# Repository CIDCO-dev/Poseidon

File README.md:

# Poseidon
Hydrographic surveying platform operating system (ROS Noetic).

## Getting started (RPi4, Ubuntu 20.04, ROS Noetic)
- Clone under `/opt`: `sudo chown $USER:$USER /opt && cd /opt && git clone --recursive <repo>`
- Install: run `install/rpi4-noetic.sh` (RPi4 target).
- Build: `cd /opt/Poseidon/src/workspace && catkin_make -j1 -DCATKIN_BLACKLIST_PACKAGES="mavros;inertial_sense;velodyne;ins_piksi;velodyne_pointcloud;velodyne_driver;velodyne_laserscan;gnss_mosaic_x5;tf"`
- Source: `source /opt/ros/noetic/setup.bash` then `source /opt/Poseidon/src/workspace/devel/setup.bash`.
- Launch simulator: `roslaunch launch/Simulator/dummy_simulator_virtual-machine.launch`, then open the web UI at `http://localhost`.

## Docs
Full documentation lives in `doc/` (Markdown):
- `doc/README.md`: overview, build, run, tests
- `doc/install.md`: installation with dependencies (RPi4, Ubuntu 20.04, ROS Noetic)

## Tests
- C++/Python/ROS: `catkin_make run_tests -j1 -DCATKIN_BLACKLIST_PACKAGES="ins_piksi;libmavconn;echoboat_odometry;mavros_msgs;mavros;mavros_extras;test_mavros;gnss_mosaic_x5;imu_bno055;sonar_imagenex852;inertial_sense;raspberrypi_vitals;imu_null;sonar_dummy;gnss_dummy;lidar_filtering"`
- JS: `cd www/webroot/js && npm test --coverage`

## Tools
- Rosbag replay: `roslaunch launch/Echoboat/rosbag_replay.launch bag_filename:=rosbag.bag`
- Lidar georef: `./devel/lib/logger/lidarGeoreferencer -h` (supports filtering options)
- Logging modes: 1=Always ON, 2=Manual, 3=Speed based

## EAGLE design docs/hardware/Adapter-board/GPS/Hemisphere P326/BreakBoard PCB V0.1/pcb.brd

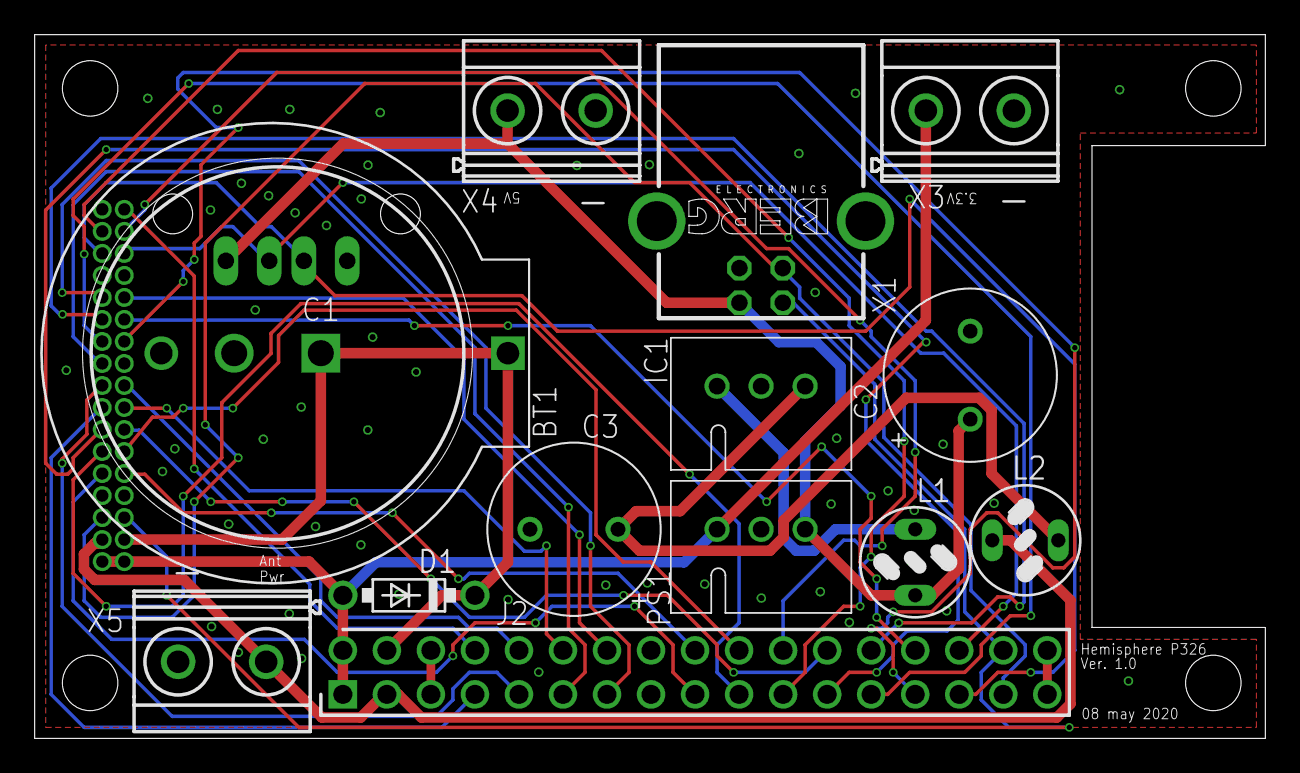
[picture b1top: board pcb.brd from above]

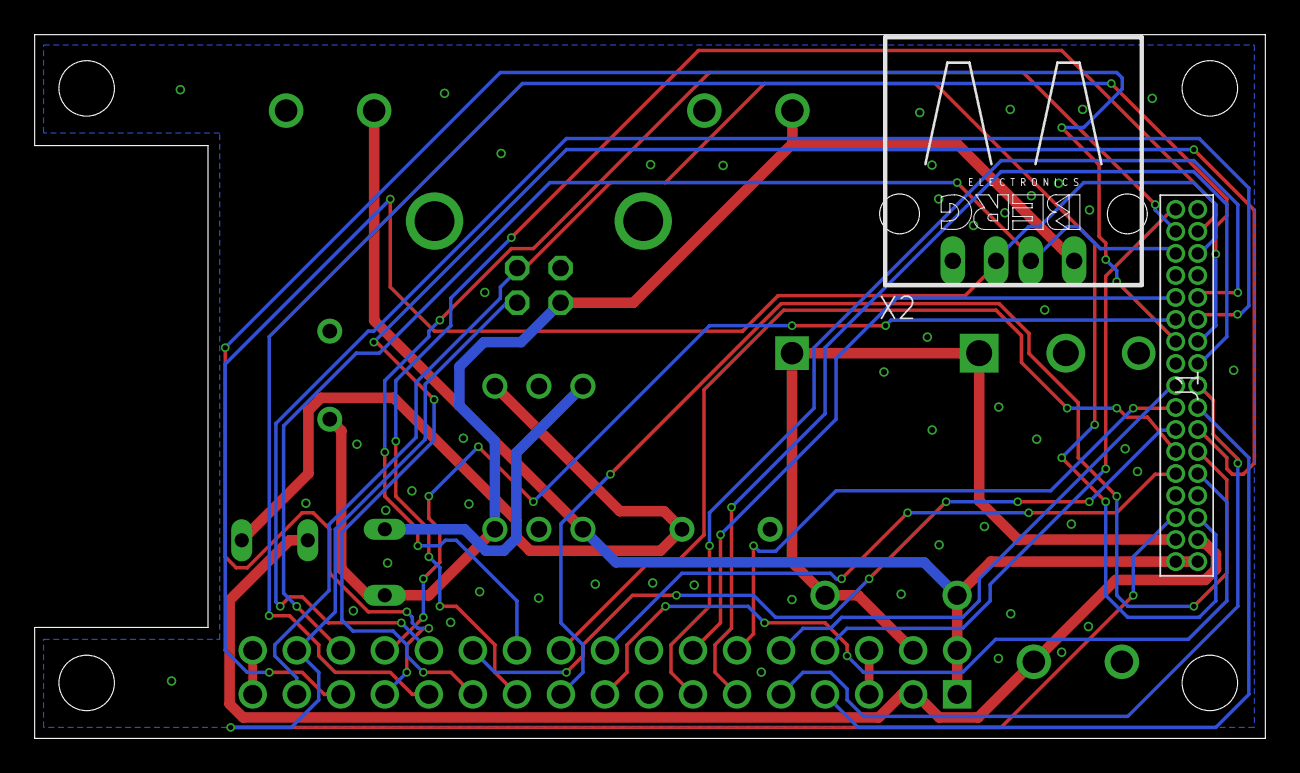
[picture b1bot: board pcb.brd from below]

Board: 4 copper layers, 71.0 x 40.6 mm, 16 parts (2 on the bottom side), 31 nets.

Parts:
BT1: 79578211
C1: DB-5R5D105T; CAPPRD500W130D2150H800
C2, C3: 22uf; CAPPRD508W65D1000H1100B
D1: 1N5817-B; DO41-7.6
IC1: OKI-78SR-5_1.5-W36-C; OKI-78SR
J1: 20021311-00034T4LF; SFMC11701LDK
J2: 67997-234HLF; HDRV34W64P254_2X17_4318X495X83
L1, L2: 10uH; 82114R
PS1: OKI-78SR-3.3_1.5-W36-C; OKI-78SR
X1: UJ2-BH-W1-TH; PN61729-S
X2: PN87520
X3, X4, X5: MKDSN1,5/2-5,08

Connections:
3.3V: D1.A, J1.1, J1.2, J2.1, J2.2, PS1.1, X3.1
5V: C2.1, L1.1, PS1.3, X1.1, X2.1, X4.1
5V_O: IC1.1, L1.2
ANT_PWR: J1.3, J2.3, L2.1, X5.1
ANT_PWR_I: C3.1, IC1.3, L2.2
BAT_BCK: BT1.1, C1.1, D1.C, J1.4, J2.4
DGPS_LOCK: J1.19, J2.11
DIF_LOCK: J1.18, J2.10
GND: BT1.2, C1.2, C2.2, C3.2, IC1.2, J1.7, J1.8, J1.27, J1.28, J2.5, J2.6, J2.15, J2.16, J2.33, J2.34, PS1.2, X1.4, X1.S1, X1.S2, X2.4, X3.2, X4.2, X5.2
GPS_LOCK: J1.17, J2.9
MM: J1.16, J2.12
PARX: J1.10, J2.18
PATX: J1.9, J2.17
PBRX: J1.12, J2.20
PBTX: J1.11, J2.19
PCRX: J1.32, J2.22
PCTX: J1.31, J2.21
PDRX: J1.14, J2.24
PDTX: J1.13, J2.23
PPS: J1.15, J2.7
RESET: J1.34, J2.8
RX_C_A: J1.23, J2.26
RX_C_B: J1.24, J2.28
SPEED_O: J1.25, J2.13
SPEED_R: J1.26, J2.14
TX_C_A: J1.21, J2.25
TX_C_B: J1.22, J2.27
USB_DEV_D+: J1.5, J2.31, X1.3
USB_DEV_D-: J1.6, J2.32, X1.2
USB_HOST_D+: J1.29, J2.29, X2.3
USB_HOST_D-: J1.30, J2.30, X2.2

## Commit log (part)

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2024-02-22 serial baud rate threaded
2024-02-22 serial baud rate
2024-02-22 serial baud rate setting
2024-02-28 water infiltration node architecture
2024-02-28 lidar calib printer
2024-02-28 fix timestamp in sonar imagenex852 py
2024-02-28 work around the python installer script
2024-02-28 create log output dir if not there
2024-02-28 fix configuration change function
2024-02-28 Issue #350
2024-02-28 fix gnss path
2024-02-28 serial number diagnostic
2024-02-28 gnss_zed-f9p_config node was not functionnal (removed form repo) in tools new python script to aply the right configuration in command line in the ZED-F9P python script to validate the configuration
2024-02-28 add missing code comment c++ code
2024-02-28 fix sonar command value
2024-02-28 fix port not getting set at launch
2024-03-14 sonar_imagenex852_c start
2024-03-25 making progress
2024-03-26 https support
2024-03-27 logging binary sonar
2024-03-27 debug binary sonar data
2024-04-02 apiKey can be changed via ui
2024-04-05 dataPoints arg imagegenex
2024-05-07 Adding helper script to replace the ssid of the Hotspot
2024-05-07 update directory in docs and add more information about the power recuirement and use in the hydroblock
2024-05-07 update docs and remove unused stuff
2024-05-09 DC-DC converter datasheet
2024-05-20 few correction in the vital node and add a collor in the status web page
2024-06-28 ssl version debug
2024-07-22 Geofence
2024-07-23 Semicolon
2024-08-05 add doccumentation in the script to set the serial number
2024-08-20 new 852 node
2024-08-29 HIH8130 chip in vitals
2024-09-03 revert change
2024-09-09 led controller
2024-09-10 logger call led controller service
2024-09-11 BinaryStreamGnssDiagnostic
2024-09-13 i2c controller + service
2024-09-16 logger led control
2024-09-17 led error triggers
2024-09-19 UI battery
2024-09-23 compile optim
2024-09-25 nofix signal + logger encapsulation
2024-09-25 fix: recording status signal do not override nofix signal
2024-10-01 initial tests ok
2024-10-02 service.waitForExistence()
2024-10-04 vitals + speed, logger text
2024-10-10 graceful shutdown
2024-10-29 #issue 389 - refactor wifi node
2024-10-31 i2c retrocompatibility
2024-11-01 Hide information in the system status web page
2024-11-01 fix geofence
2024-11-04 ROS is adding 2 param to each argv
2024-11-14 comment some ros messageto reduce log size
2024-11-18 Add fixes made by Patrick and add information hiden in the web page if the i1c sensor are not present
2024-11-21 fix ros error message
2024-11-22 fixe web interface for missing sensors
2024-11-22 fix in websocket and javascript for webinterface for #407
2024-11-22 work map.html for #408
2024-11-22 more work on javascript for #408
2024-11-22 more work on #408
2024-11-22 fix web page
2024-11-27 add button for Auto pan to current position
2024-11-28 add js script for wicket and terraformer to be able to be loaded locally
2024-12-02 Update User manual screen capture.
2025-02-10 fix error
2025-02-10 add new dataset in websocket
2025-02-10 fix led state
2025-02-11 move the code in the right function
2025-02-11 update battery formula on status webpage
2025-02-11 remove the loffing of the error
2025-02-11 fix error on sonar no value
2025-02-11 code cleaning
2025-02-11 HydroBlock Installation Manual and User Manual HydroBlock PCB Rev 1 Led Module PCB Rev 0
2025-02-11 Cleaning directory
2025-02-11 HydroB PCB Rev 0.3 Module bypass rev 1.0 Module power rev 1.0
2025-02-11 HydroB rev 0.5
2025-02-11 Firmware for the power module of the hydroball
2025-02-11 Led driver Obsolete, led is drived directly by gpio
2025-02-12 fix nodes to control eht led with the GPIO
2025-02-12 PCB Production files
2025-02-27 update the power module programmer interface to be able to power the power module from a usb port if programmed with an atmel ice programmer
2025-02-27 PCB HB-HAT : fix mosfet pinout
2025-03-04 incrase debug output
2025-03-04 update warning and critical message for the web interface
2025-03-05 no led at boot when we alredy have gps fix
2025-03-05 fix the condition for the humidity on the web interface
2025-03-10 fix condition for shut down and translate and update the comment
2025-03-19 fix battery voltage treshold
2025-03-19 fix voltage bar on the system status web page
2025-03-19 fix the battery voltage from 13.5 to 11.9v in the web interface
2025-04-10 fix i2c4 configuration
2025-04-22 add gnss telemetry in the node of the zed-f9p
2025-04-23 gnss status on the dashboard working
2025-04-24 first file transfered manualy by the web interface
2025-04-24 fix dependencu for curl
2025-05-14 fix 500ms offset betwen systemclock and gnss clock
2025-08-26 diagnostics
2025-11-07 cpp_import
2025-12-01 fix ICMP ping from google to ubuntu, to reduce the amount of host route.
2025-12-01 fix sonar node name
2025-12-01 install git in the ci
2025-12-01 add ros-noetic-roslint ros-noetic-nodelet ros-noetic-dynamic-reconfigure ros-noetic-sensor-msgs in the ci installation
2025-12-01 fix binairy logger variable location and test
2025-12-01 add node list and test script
2025-12-01 add ros-noetic-sbg-driver in the CI installation
2025-12-01 add func list in manifest.md
2025-12-01 blacklist imu_bno055 node and rpivitals fix launch file for the logger test
2025-12-01 fix dependency for file websocket
2025-12-01 first test for the workflow
2025-12-01 add libwebsocketpp-dev in the ci installation
2025-12-01 add libopencv-dev libexiv2-dev libboost-signals-dev to ci installation
2025-12-01 add definition in data websocket test
2025-12-01 fix source error in the ci
2025-12-01 fix dependencies and force catkinmake in -j1
2025-12-01 remove libboost-signals-dev from ci installation
2025-12-01 fix requirement for the logger test
2025-12-01 add a dep for test purpose
2025-12-01 test correction for logger service
2025-12-01 add nmea0183 test
2025-12-01 add filwwebsocket in blacklist
2025-12-01 add test in the nmea0183 node
2025-12-01 Fix build dep and ci
2025-12-01 fix dependencies(
2025-12-01 JS tests: added explicit `jest-environment-jsdom` devDependency to satisfy Jest config.
2025-12-01 JS housekeeping: generated package-lock for reproducible installs and removed committed coverage output; keep coverage artifacts untracked.
2025-12-01 - Fixed logger text test build by defining `currentRssBytes` helper in `test_logger_text_node.cpp`.
2025-12-01 Logger: transfer loop now counts zip files once, reports status, sends, and removes on success; RapidJSON string creation simplified.
2025-12-01 - Updated agent guidelines: C++ formatting/lint (`clang-format`, `clang-tidy`) now tracked in the Review & PR checklist. - Updated agent guidelines: Python formatting (`black`) added to the Review & 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
2025-12-01 CI: Coverage summary now runs from a separate script `.github/workflows/scripts/coverage_summary.py`.
2025-12-01 CI: GitHub Actions now posts C++/Python/JS coverage summary to the workflow summary.
2025-12-01 fix dependencies...
2025-12-01 add dependencies and fix logger test
2025-12-01 add tests on logger node
2025-12-01 CI: Coverage summary heredoc anchored with indentation (python block).
2025-12-01 Build fix: added `binary_stream_msg` dependency to diagnostics package (resolves missing `binary_stream_msg/Stream.h` include).
2025-12-01 Docs: added `doc/install.md` detailing prerequisites and install steps for RPi4 Ubuntu 20.04.
2025-12-01 JS: VM-based Jest tests now instrument scripts before execution so coverage is reported correctly (no longer 0%).
2025-12-01 CI: coverage summary now also falls back to JS lcov when coverage-summary.json is missing (ensures JS coverage is reported).
2025-12-01 CI: coverage summary surfaces test totals/errors/failures and lists failing suites (links to junit-test-results artifact).
2025-12-01 Remove ROS1→ROS2 port attempt
2025-12-01 raspberrypi_vitals: ensure targets depend on generated messages (catkin_EXPORTED_TARGETS) and declare i2c_controller_service in CATKIN_DEPENDS to fix missing `raspberrypi_vitals_msg/sysinfo.h` during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
2025-12-01 cleaning of diagnostics
2025-12-01 - diagnostics: install the websocket integration test script via catkin so rostest can locate/execute it. - ROS tests: add pytest skip guards for ROS-dependent Python tests to avoid failures when ROS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
2025-12-01 Launch: replace missing `diagnostics_node` with `diagnostics_websocket.py` in Hydrobox/Hydroball/Simulator launch files to fix diagnostics startup errors.
2025-12-01 diagnostics: fix `getRunningNodes` handler to unpack publisher/subscriber/service lists correctly (no more "too many values to unpack").
2025-12-02 - Web UI: System Status now shows wlan0 state + SSID using sysfs/proc+iwgetid (no nmcli dependency in telemetry path). - hydroball_data_websocket: publish Wi‑Fi status/SSID in telemetry payload (`tel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
2025-12-02 - diagnostics: added unit tests for the diagnostics websocket node (commands, node listing, lifecycle helpers) to cover its behaviors without ROS master dependencies.
2025-12-02 - install: fixed `ethernet_move_hotspot_rpi4.sh` variable handling (no more escaped `$`/awk errors) and robust interface-name replacement in Hotspot.nmconnection.
2025-12-02 launch: All Hydrobox profiles now start `wifi_file_transfer_config_node` so Wi‑Fi provisioning is consistent across RPi/Rock and simulator setups.
2025-12-02 - hydroball_data_websocket: use nmcli to populate Wi‑Fi SSID/state, drop iwgetid dependency, and clear SSID when disconnected.
2025-12-02 - Web UI (status): Wi‑Fi row now matches other bars (full-width gradient green/red) with SSID in the header and connection state inline, instead of a separate dot/text block.
2025-12-02 - Web UI (status): Wi‑Fi row matches other bars (full-width gradient green/red) with SSID + state inline in the header; bar color now follows `wifi.state` up/down.
2025-12-09 - diagnostics: added end-to-end nosetest that launches `launchROSService.sh`, waits for the 9099 diagnostics websocket, sends `updateDiagnostic`, and validates the returned payload; optional DBT feed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
2025-12-18 - diagnostics: start the WebSocket server from inside the asyncio loop to be compatible with newer `websockets` versions (fixes port 9099 not opening on some systems).
2025-12-18 - launch/e2e: pass `loggerPath` and `configPath` from `POSEIDON_LOGGER_PATH` / `POSEIDON_CONFIG_PATH` via `launchROSService.sh` (avoids invalid nested `$(optenv ...)` substitutions in roslaunch args).
2025-12-18 - diagnostics/e2e: make IMU/sonar communication thresholds configurable via env vars (`POSEIDON_DIAG_IMU_*`, `POSEIDON_DIAG_SONAR_*`) to reduce false negatives on slower benches. - e2e: allow tuning 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
2025-12-18 - e2e: keep a DBT NMEA writer running for the whole E2E so `/depth` can be validated when `DIAGNOSTICS_FAKE_SERIAL_PORT` is available. - e2e: optional exclusive mode (`POSEIDON_E2E_EXCLUSIVE=1`) stop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
2026-01-12 - e2e: require root launch by default (`POSEIDON_E2E_LAUNCH_AS_ROOT=1`) and reuse the already-started service during the E2E run to avoid duplicate roslaunch. - diagnostics/e2e: honor `POSEIDON_E2E_L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
2026-02-28 Bump minimatch from 3.1.2 to 3.1.5 in /www/webroot/js
    Bumps [minimatch](https://github.com/isaacs/minimatch) from 3.1.2 to 3.1.5.
    - [Changelog](https://github.com/isaacs/minimatch/blob/main/changelog.md)
    - [Commits](https://github.com/isaacs/minimatch/compare/v3.1.2...v3.1.5)
    ---
    updated-dependencies:
    - dependency-name: minimatch
